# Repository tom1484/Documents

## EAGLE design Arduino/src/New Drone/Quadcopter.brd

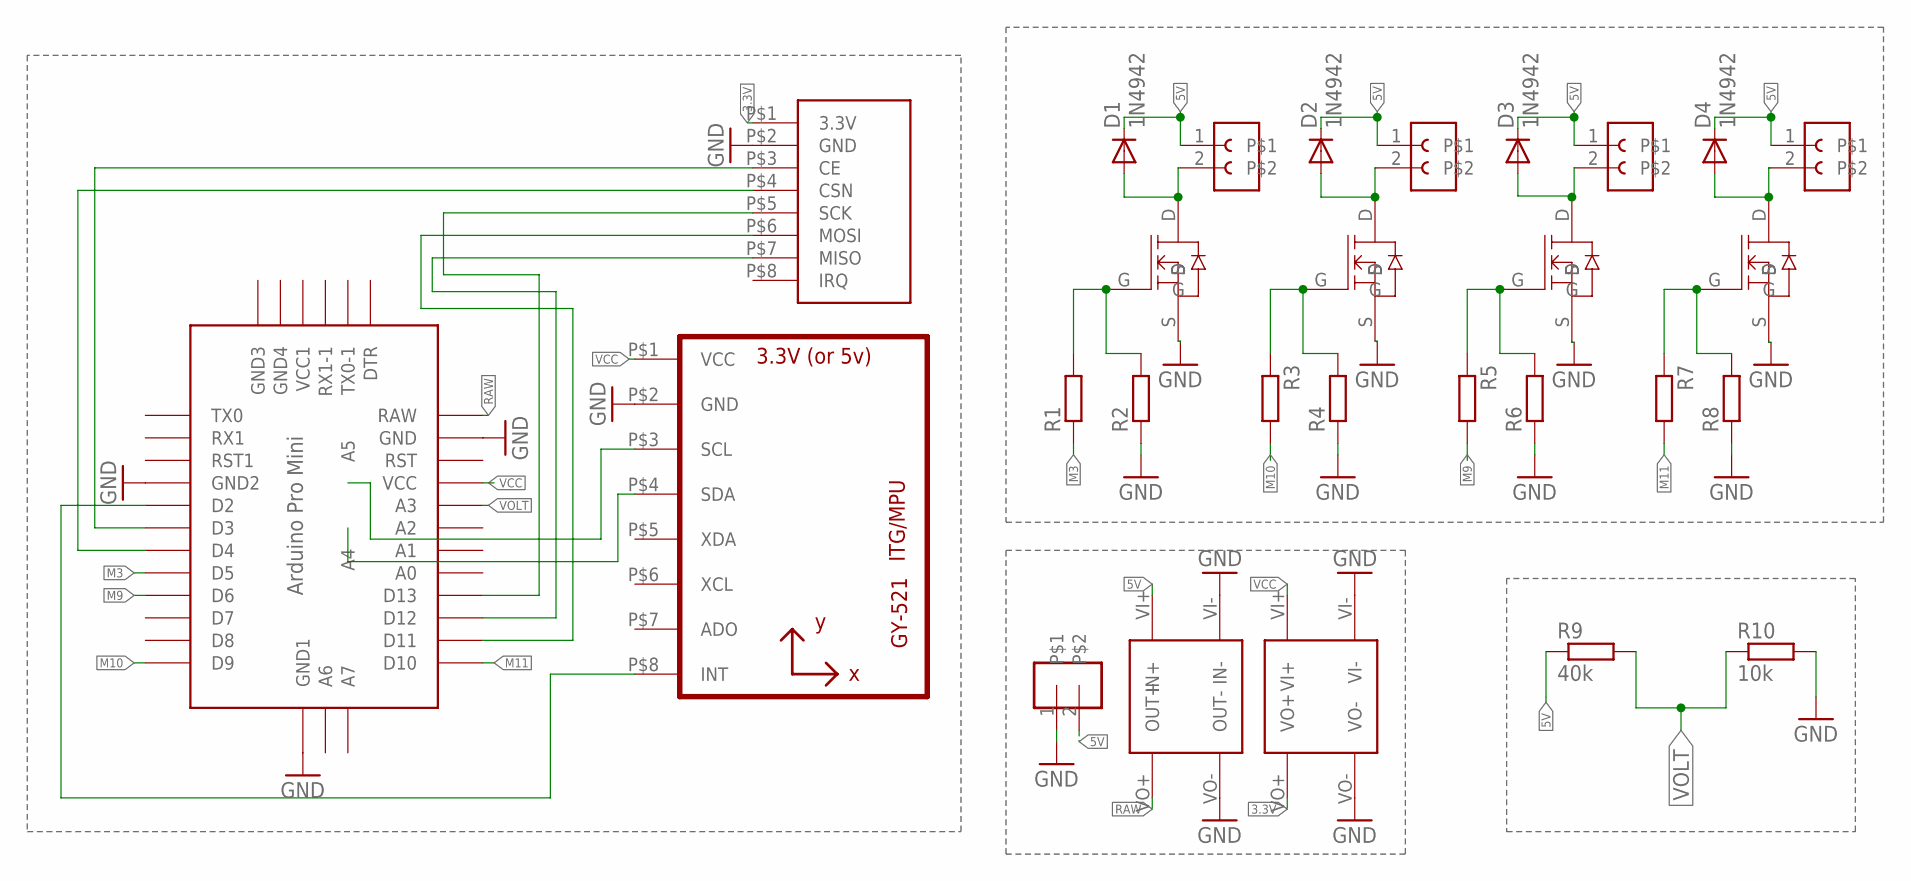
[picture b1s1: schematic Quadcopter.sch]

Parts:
D1, D2, D3, D4: 1N4942; DO41-10
R1, R2, R3, R4, R5, R6, R7, R8: R-EU_R1206; R1206
R9: 40k; R1206
R10: 10k; R1206
U2: GY-521MPU6050; GY-521
U$1, U$2, U$3, U$9: FE02
U$4: ABK-PRO-MINI
U$5, U$7, U$8, U$10: SI2306
U$6: 02; FE05-1
U$11: NRF24L01
U$12: 3.3V
U$13: 5V

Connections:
3.3V: U$11.P$1 (3.3V), U$12.VO+
5V: D1.C, D2.C, D3.C, D4.C, R9.1, U$1.1, U$2.1, U$3.1, U$6.2, U$9.1, U$13.VI+ (IN+)
GND: R2.1, R4.1, R6.1, R8.1, R10.2, U2.P$2 (GND), U$4.P$10 (GND2), U$4.P$20 (GND), U$4.P$33 (GND1), U$5.S, U$6.1, U$7.S, U$8.S, U$10.S, U$11.P$2 (GND), U$12.VI-, U$12.VO-, U$13.VI- (IN-), U$13.VO- (OUT-)
M3: R1.1, U$4.P$14 (D5)
M9: R5.2, U$4.P$15 (D6)
M10: R3.2, U$4.P$18 (D9)
M11: R7.2, U$4.P$30 (D10)
unnamed: R1.2, R2.2, U$7.G
unnamed: D1.A, U$3.2, U$7.D
unnamed: R3.1, R4.2, U$8.G
unnamed: D2.A, U$1.2, U$8.D
unnamed: R5.1, R6.2, U$10.G
unnamed: D3.A, U$9.2, U$10.D
unnamed: R7.1, R8.2, U$5.G
unnamed: D4.A, U$2.2, U$5.D
unnamed: U$4.P$12 (D3), U$11.P$3 (CE)
unnamed: U$4.P$13 (D4), U$11.P$4 (CSN)
unnamed: U$4.P$27 (D13), U$11.P$5 (SCK)
unnamed: U$4.P$28 (D12), U$11.P$7 (MISO)
unnamed: U$4.P$29 (D11), U$11.P$6 (MOSI)
unnamed: U2.P$8 (INT), U$4.P$11 (D2)
unnamed: U2.P$3 (SCL), U$4.P$34 (A5)
unnamed: U2.P$4 (SDA), U$4.P$35 (A4)
RAW: U$4.P$19 (RAW), U$13.VO+ (OUT+)
VCC: U2.P$1 (VCC), U$4.P$22 (VCC), U$12.VI+
VOLT: R9.2, R10.1, U$4.P$23 (A3)

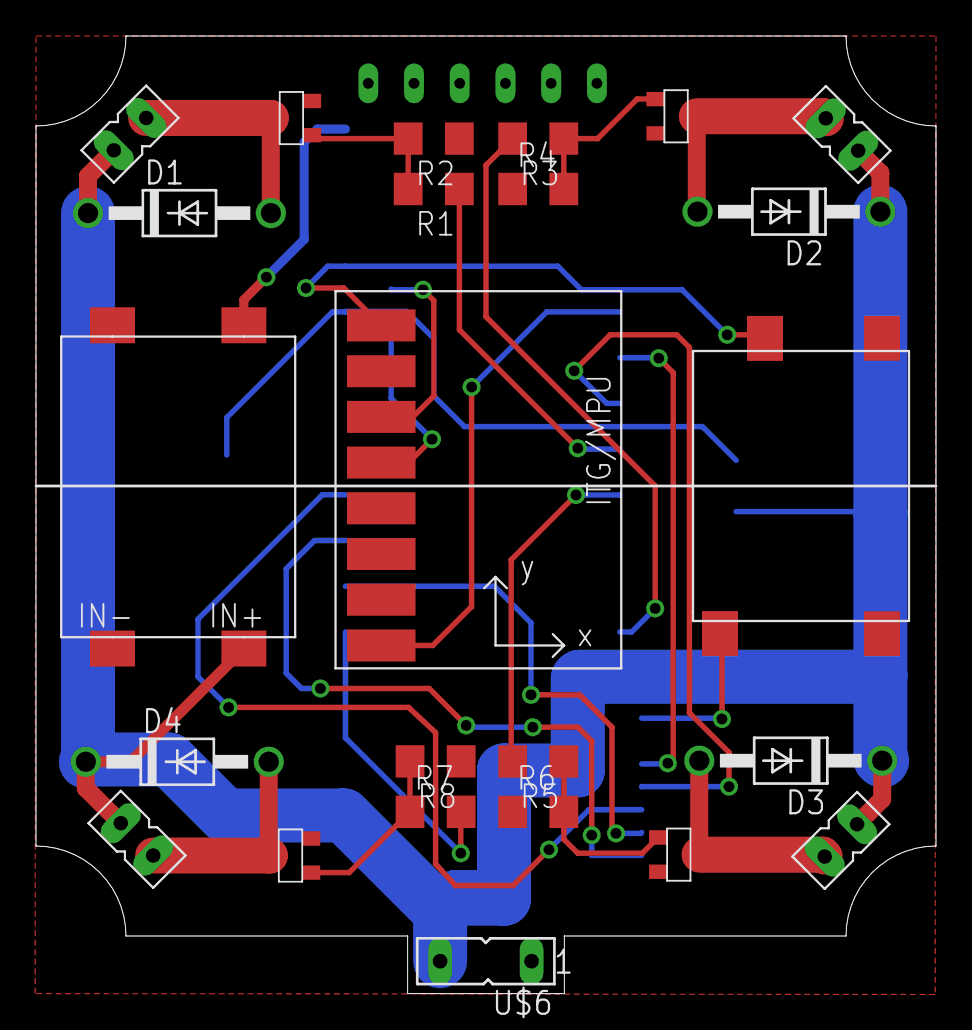
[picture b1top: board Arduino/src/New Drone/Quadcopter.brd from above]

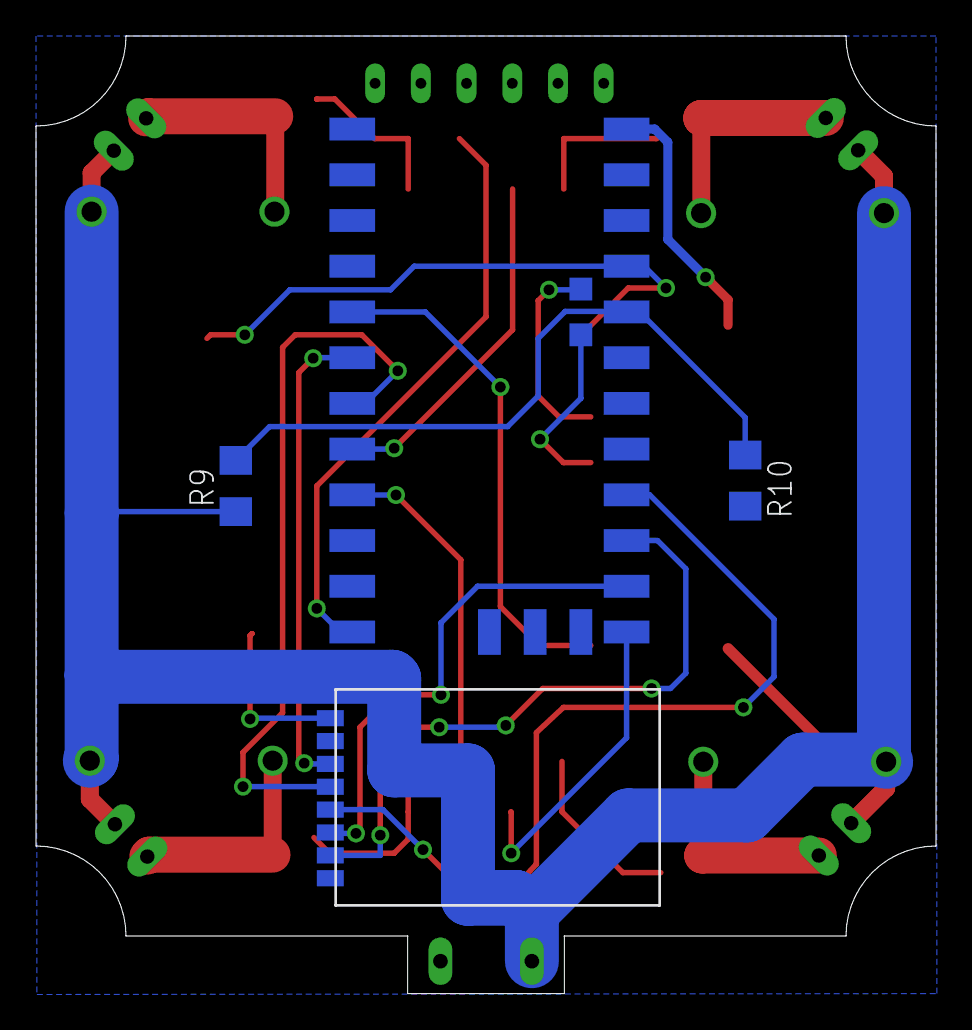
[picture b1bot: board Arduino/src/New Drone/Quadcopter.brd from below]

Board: 2 copper layers, 50.0 x 53.2 mm, 28 parts (4 on the bottom side), 26 nets.

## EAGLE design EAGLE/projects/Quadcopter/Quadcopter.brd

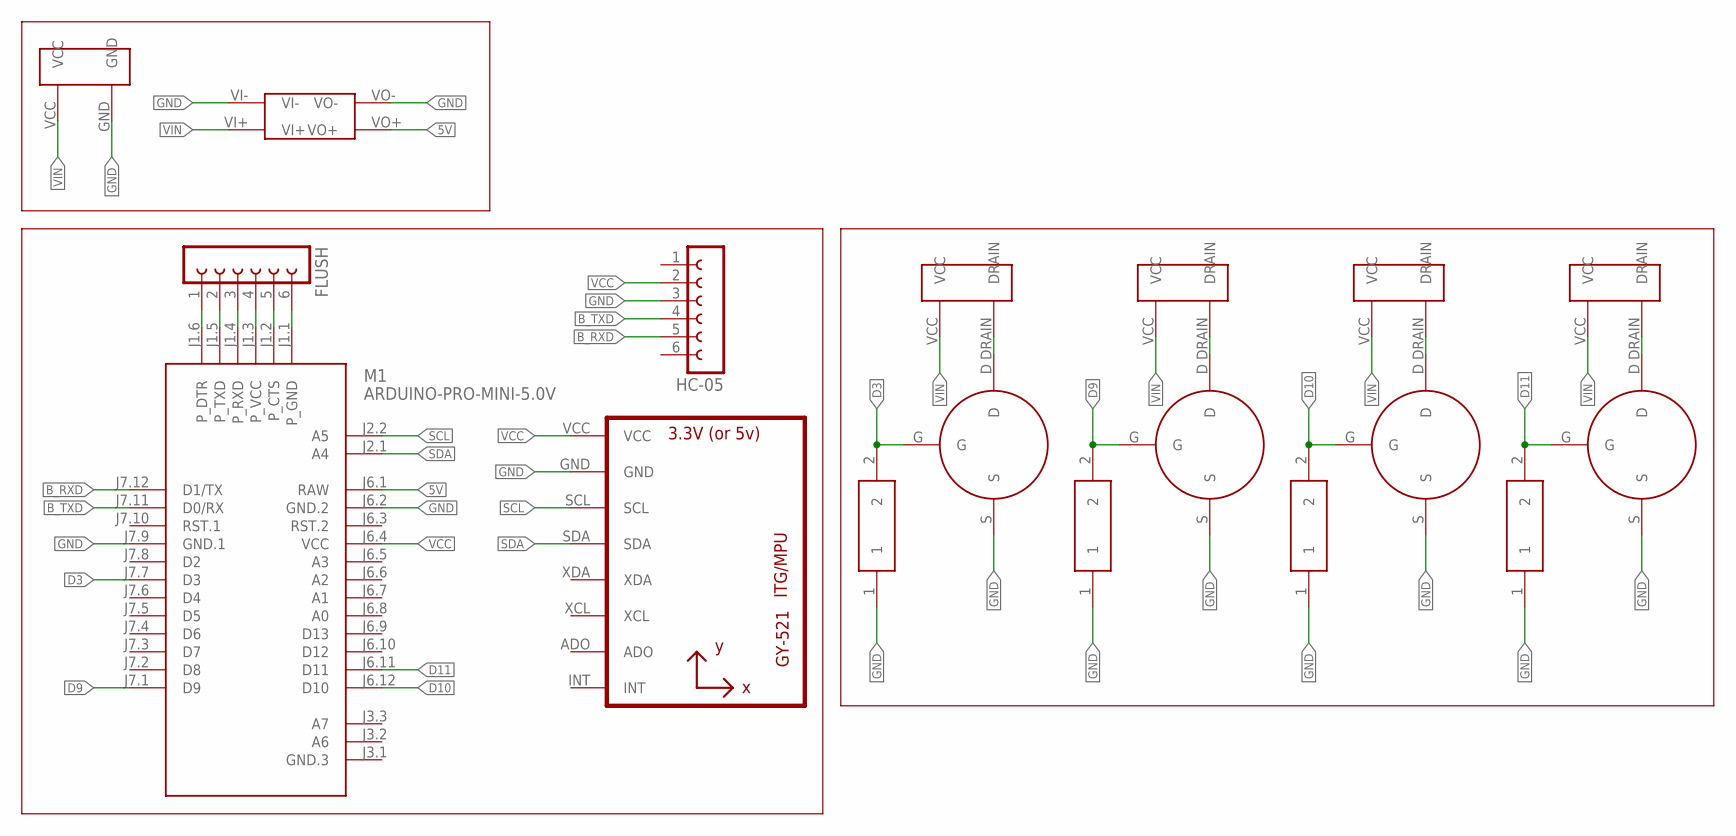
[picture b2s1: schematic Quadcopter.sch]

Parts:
FLUSH: FE06-1; FE06
HC-05: FE06-1; FE06
M1: ARDUINO-PRO-MINI-5.0V; ARDUINO-PRO-MINI
U1: GY-521MPU6050; GY-521
U$1, U$6, U$9, U$12: SI2306
U$2, U$7, U$10, U$13: 1206_RESISTOR
U$3: 5V_TRANSFORMER
U$4: POWER_MAIN
U$5, U$8, U$11, U$14: POWER_MOTOR

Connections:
5V: M1.J6.1 (RAW), U$3.VO+
B_RXD: HC-05.5, M1.J7.12 (D1/TX)
B_TXD: HC-05.4, M1.J7.11 (D0/RX)
D3: M1.J7.7 (D3), U$1.G, U$2.2
D9: M1.J7.1 (D9), U$6.G, U$7.2
D10: M1.J6.12 (D10), U$9.G, U$10.2
D11: M1.J6.11 (D11), U$12.G, U$13.2
GND: HC-05.3, M1.J6.2 (GND.2), M1.J7.9 (GND.1), U1.GND, U$1.S, U$2.1, U$3.VI-, U$3.VO-, U$4.GND, U$6.S, U$7.1, U$9.S, U$10.1, U$12.S, U$13.1
unnamed: FLUSH.1, M1.J1.6 (P_DTR)
unnamed: U$6.D, U$8.DRAIN
unnamed: FLUSH.2, M1.J1.5 (P_TXD)
unnamed: U$9.D, U$11.DRAIN
unnamed: U$1.D, U$5.DRAIN
unnamed: FLUSH.3, M1.J1.4 (P_RXD)
unnamed: U$12.D, U$14.DRAIN
unnamed: FLUSH.4, M1.J1.3 (P_VCC)
unnamed: FLUSH.5, M1.J1.2 (P_CTS)
unnamed: FLUSH.6, M1.J1.1 (P_GND)
SCL: M1.J2.2 (A5), U1.SCL
SDA: M1.J2.1 (A4), U1.SDA
VCC: HC-05.2, M1.J6.4 (VCC), U1.VCC
VIN: U$3.VI+, U$4.VCC, U$5.VCC, U$8.VCC, U$11.VCC, U$14.VCC

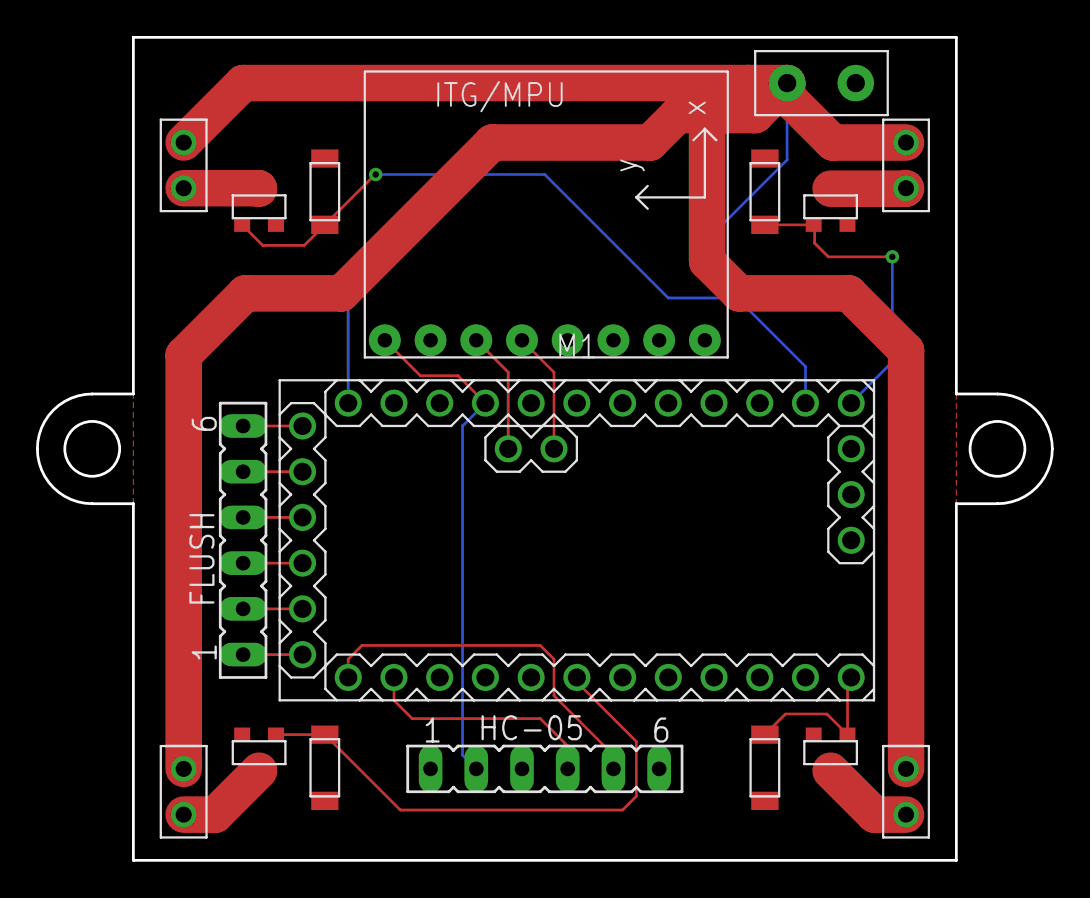
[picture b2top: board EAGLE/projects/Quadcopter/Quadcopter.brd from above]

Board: 2 copper layers, 56.4 x 45.7 mm, 18 parts (1 on the bottom side), 22 nets.

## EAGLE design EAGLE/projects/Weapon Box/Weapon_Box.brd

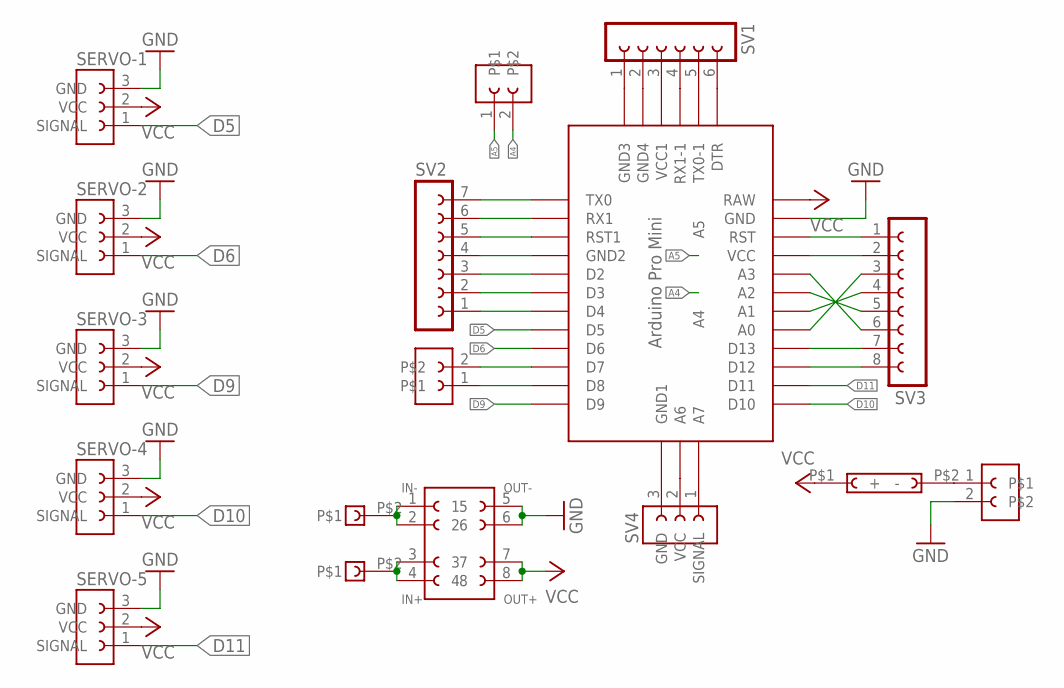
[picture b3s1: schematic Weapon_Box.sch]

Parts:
SERVO-1, SERVO-2, SERVO-3, SERVO-4, SERVO-5: FE05-1
SV1: FE06-1; FE06
SV2: FE07-1; FE07
SV3: FE08-1; FE08
SV4: FE05-1
U$1: ABK-PRO-MINI
U$2: ROWER_SUPPLY
U$3, U$7, U$8: FE02
U$4, U$5: 2018
U$6: 330

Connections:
A4: U$1.A4, U$8.2
A5: U$1.A5, U$8.1
D5: SERVO-1.1 (SIGNAL), U$1.D5
D6: SERVO-2.1 (SIGNAL), U$1.D6
D9: SERVO-3.1 (SIGNAL), U$1.D9
D10: SERVO-4.1 (SIGNAL), U$1.D10
D11: SERVO-5.1 (SIGNAL), U$1.D11
GND: SERVO-1.3 (GND), SERVO-2.3 (GND), SERVO-3.3 (GND), SERVO-4.3 (GND), SERVO-5.3 (GND), U$1.GND, U$2.5, U$2.6, U$7.2
unnamed: SV1.1, U$1.GND2 (GND3)
unnamed: SV1.2, U$1.GND3 (GND4)
unnamed: SV1.3, U$1.VCC1
unnamed: SV1.4, U$1.RX1-1
unnamed: SV1.5, U$1.TX0-1
unnamed: SV1.6, U$1.DTR
unnamed: SV2.1, U$1.D4
unnamed: SV2.2, U$1.D3
unnamed: SV2.3, U$1.D2
unnamed: SV2.4, U$1.GND1 (GND2)
unnamed: SV2.5, U$1.RST1
unnamed: SV2.6, U$1.RX1
unnamed: SV2.7, U$1.TX0
unnamed: SV3.6, U$1.A3
unnamed: SV3.3, U$1.A0
unnamed: SV3.5, U$1.A2
unnamed: SV3.4, U$1.A1
unnamed: SV3.1, U$1.RST
unnamed: SV3.2, U$1.VCC
unnamed: SV3.7, U$1.D13
unnamed: SV3.8, U$1.D12
unnamed: SV4.1 (SIGNAL), U$1.A7
unnamed: SV4.2 (VCC), U$1.A6
unnamed: SV4.3 (GND), U$1.GND4 (GND1)
unnamed: U$1.D8, U$3.1
unnamed: U$1.D7, U$3.2
unnamed: U$2.3, U$2.4, U$5.P$2
unnamed: U$6.P$2 (-), U$7.1
unnamed: U$2.1, U$2.2, U$4.P$2
VCC: SERVO-1.2 (VCC), SERVO-2.2 (VCC), SERVO-3.2 (VCC), SERVO-4.2 (VCC), SERVO-5.2 (VCC), U$1.RAW, U$2.7, U$2.8, U$6.P$1 (+)

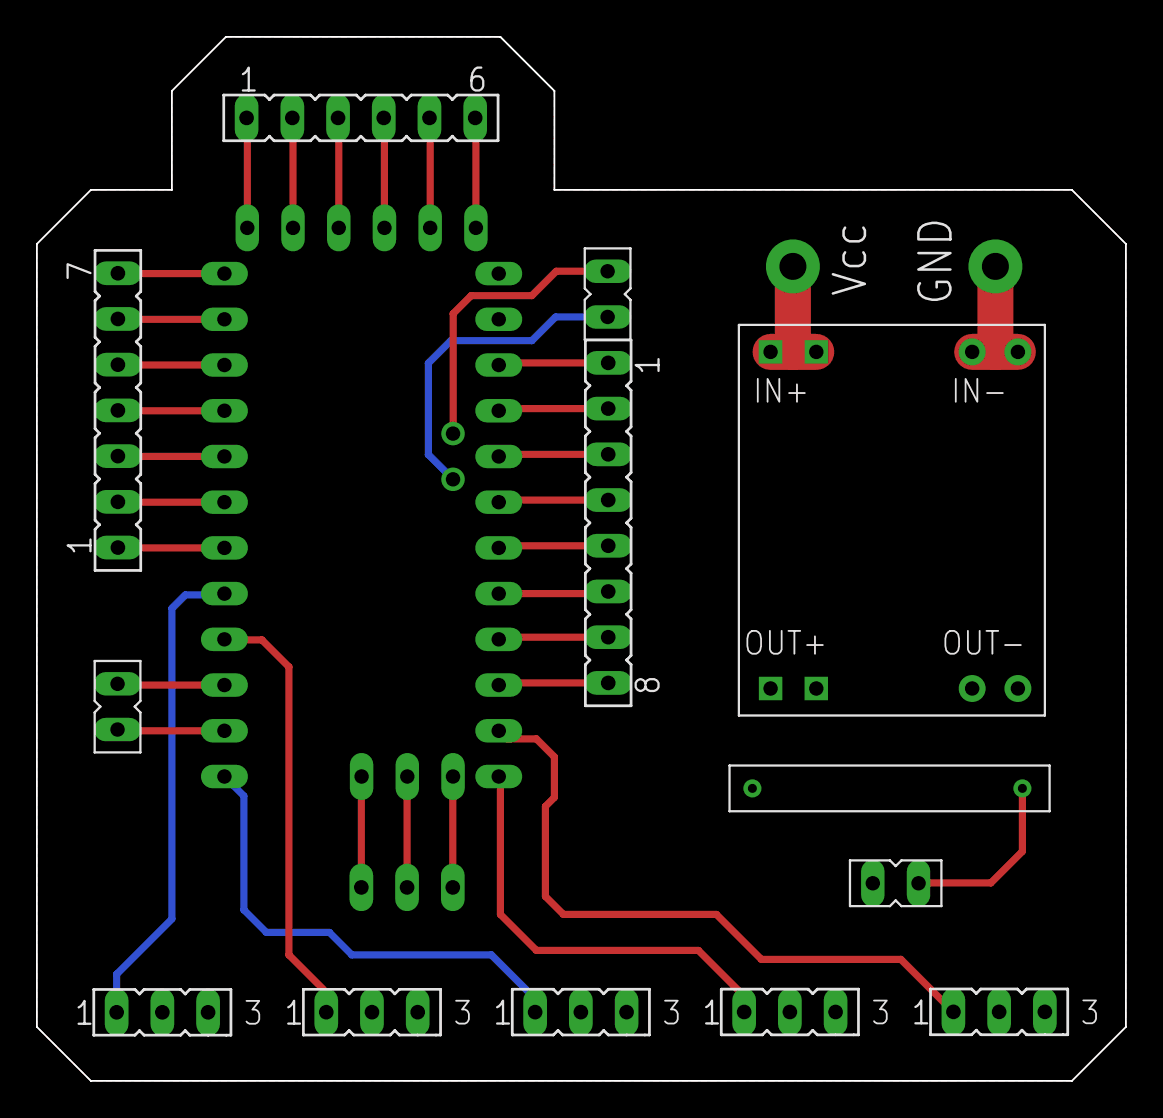
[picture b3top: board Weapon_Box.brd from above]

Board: 2 copper layers, 60.5 x 58.0 mm, 17 parts (1 on the bottom side), 38 nets.

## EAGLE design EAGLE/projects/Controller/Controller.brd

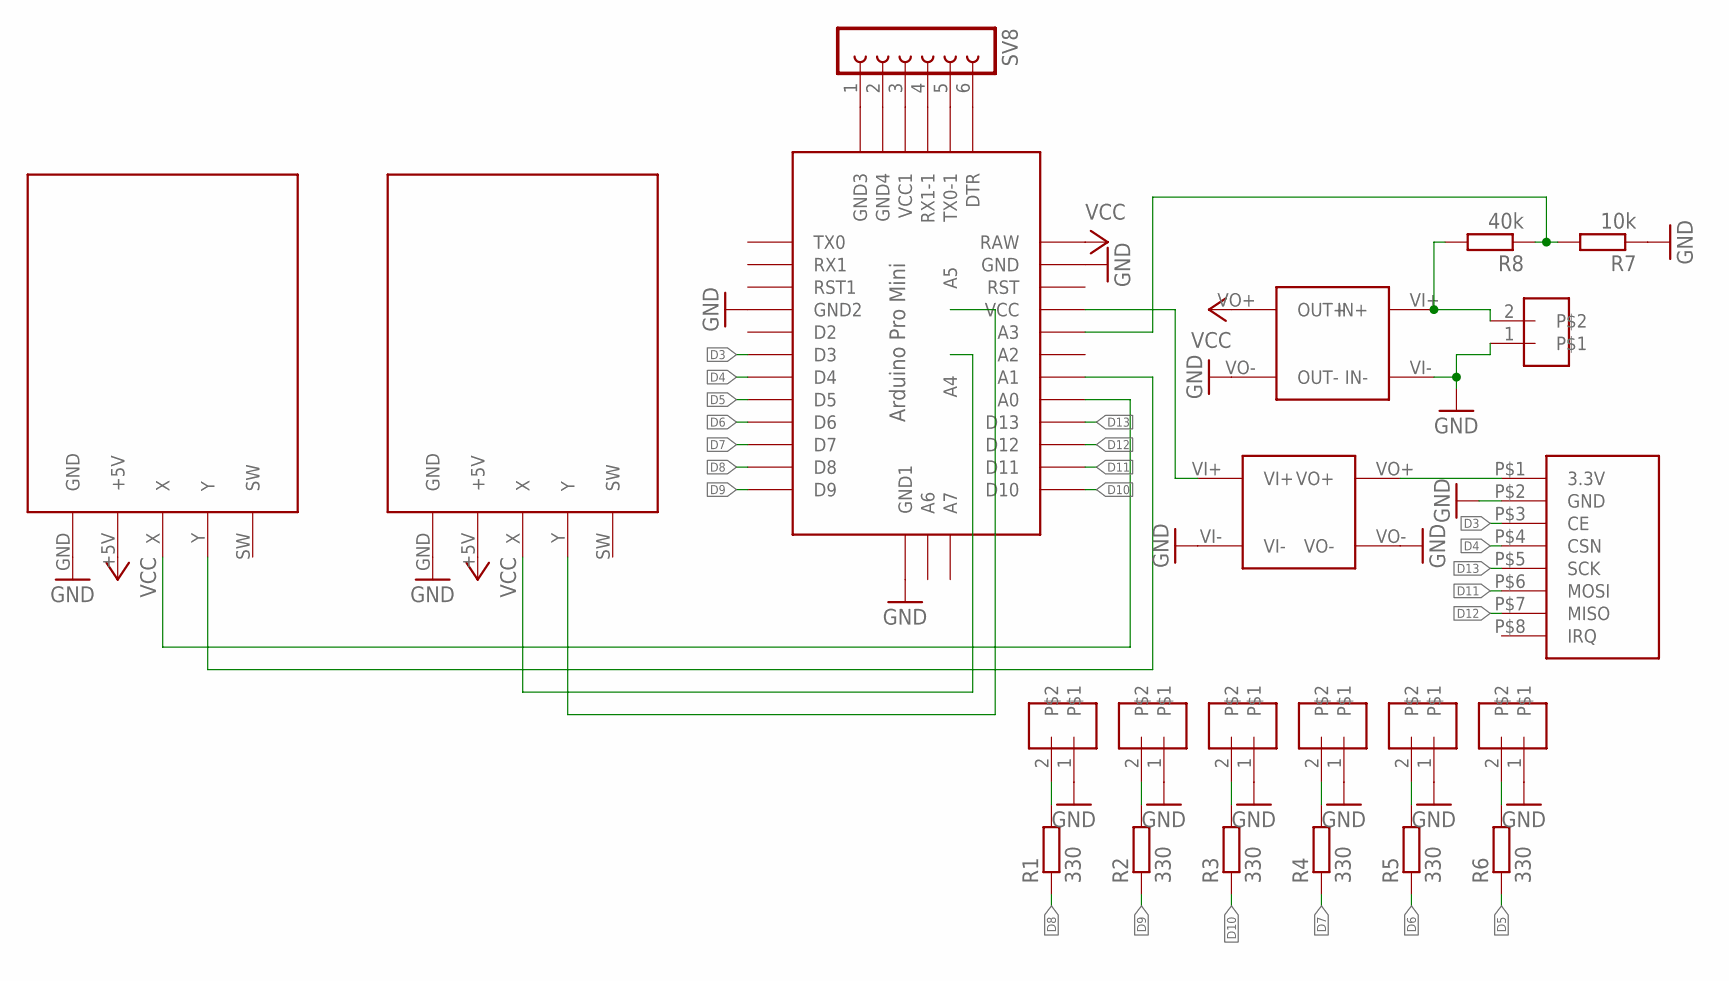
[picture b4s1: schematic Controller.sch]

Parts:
R1, R2, R3, R4, R5, R6: 330; R1206
R7: 10k; R1206
R8: 40k; R1206
SV1, SV2, SV3, SV4, SV5, SV6, SV7: FE05-1
SV8: FE06-1; FE06
U$1, U$2: JOYSTICK
U$4: ABK-PRO-MINI
U$5: NRF24L01
U$7: 3.3V
U$8: 5V

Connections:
D3: U$4.P$12 (D3), U$5.P$3 (CE)
D4: U$4.P$13 (D4), U$5.P$4 (CSN)
D5: R6.1, U$4.P$14 (D5)
D6: R5.1, U$4.P$15 (D6)
D7: R4.1, U$4.P$16 (D7)
D8: R1.1, U$4.P$17 (D8)
D9: R2.1, U$4.P$18 (D9)
D10: R3.1, U$4.P$30 (D10)
D11: U$4.P$29 (D11), U$5.P$6 (MOSI)
D12: U$4.P$28 (D12), U$5.P$7 (MISO)
D13: U$4.P$27 (D13), U$5.P$5 (SCK)
GND: R7.1, SV1.1, SV2.1, SV3.1, SV4.1, SV5.1, SV6.1, SV7.1, U$1.GND, U$2.GND, U$4.P$10 (GND2), U$4.P$20 (GND), U$4.P$33 (GND1), U$5.P$2 (GND), U$7.VI-, U$7.VO-, U$8.VI- (IN-), U$8.VO- (OUT-)
unnamed: U$1.X, U$4.P$26 (A0)
unnamed: U$1.Y, U$4.P$25 (A1)
unnamed: U$2.X, U$4.P$35 (A4)
unnamed: U$2.Y, U$4.P$34 (A5)
unnamed: R8.2, SV1.2, U$8.VI+ (IN+)
unnamed: U$4.P$22 (VCC), U$7.VI+
unnamed: U$5.P$1 (3.3V), U$7.VO+
unnamed: R1.2, SV7.2
unnamed: R2.2, SV6.2
unnamed: R3.2, SV5.2
unnamed: R4.2, SV4.2
unnamed: R5.2, SV3.2
unnamed: R6.2, SV2.2
unnamed: R7.2, R8.1, U$4.P$23 (A3)
unnamed: SV8.1, U$4.P$1 (GND3)
unnamed: SV8.2, U$4.P$2 (GND4)
unnamed: SV8.3, U$4.P$3 (VCC1)
unnamed: SV8.4, U$4.P$4 (RX1-1)
unnamed: SV8.5, U$4.P$5 (TX0-1)
unnamed: SV8.6, U$4.P$6 (DTR)
VCC: U$1.+5V, U$2.+5V, U$4.P$19 (RAW), U$8.VO+ (OUT+)

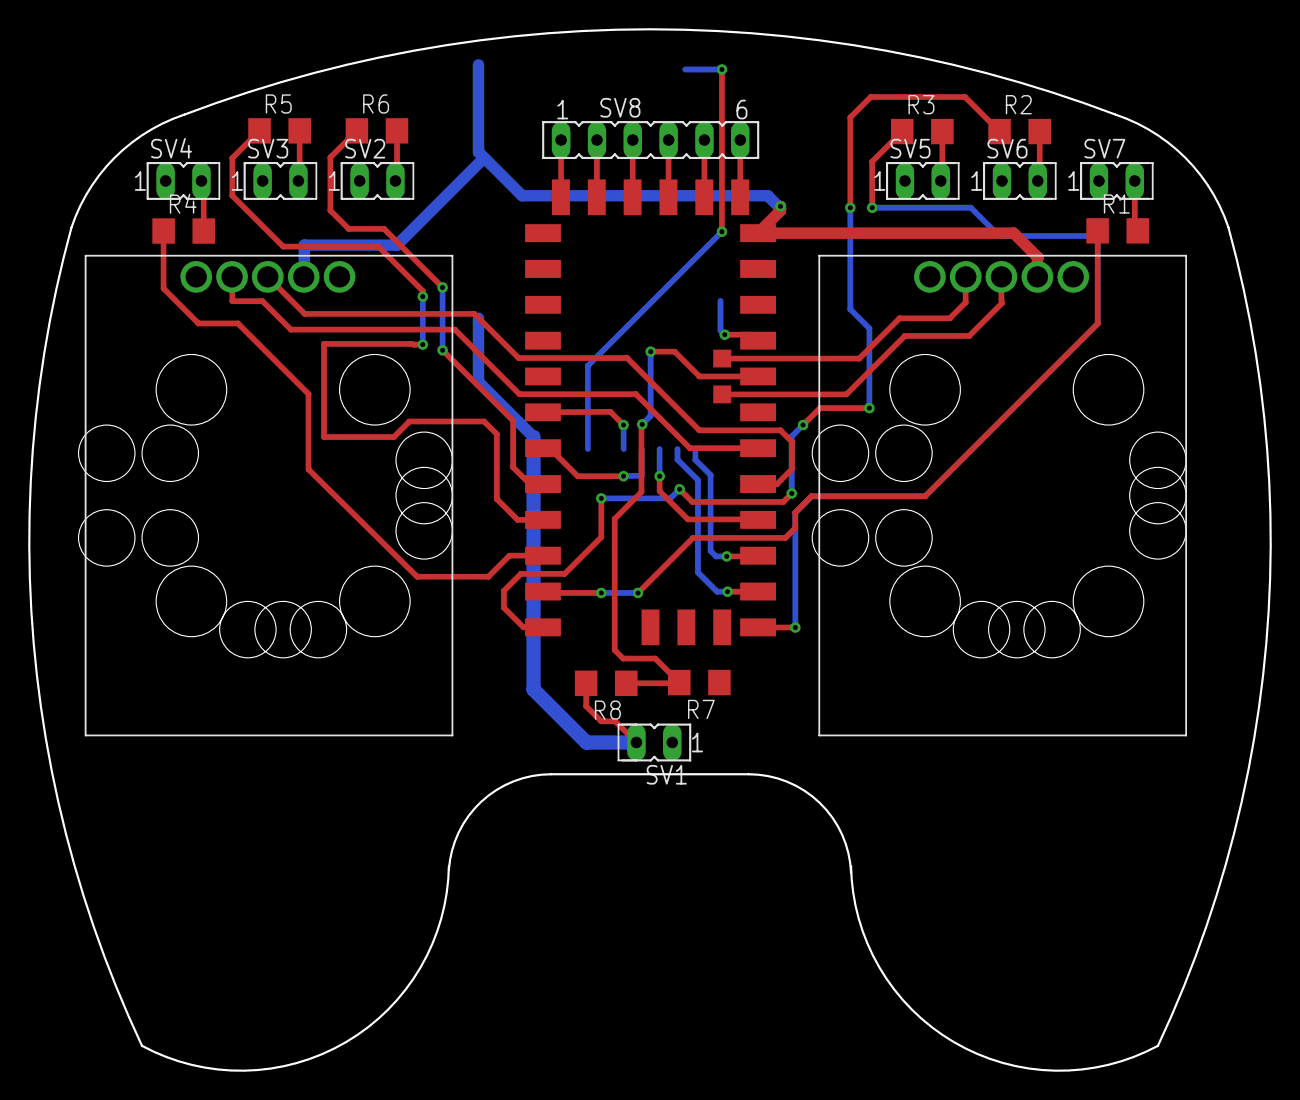
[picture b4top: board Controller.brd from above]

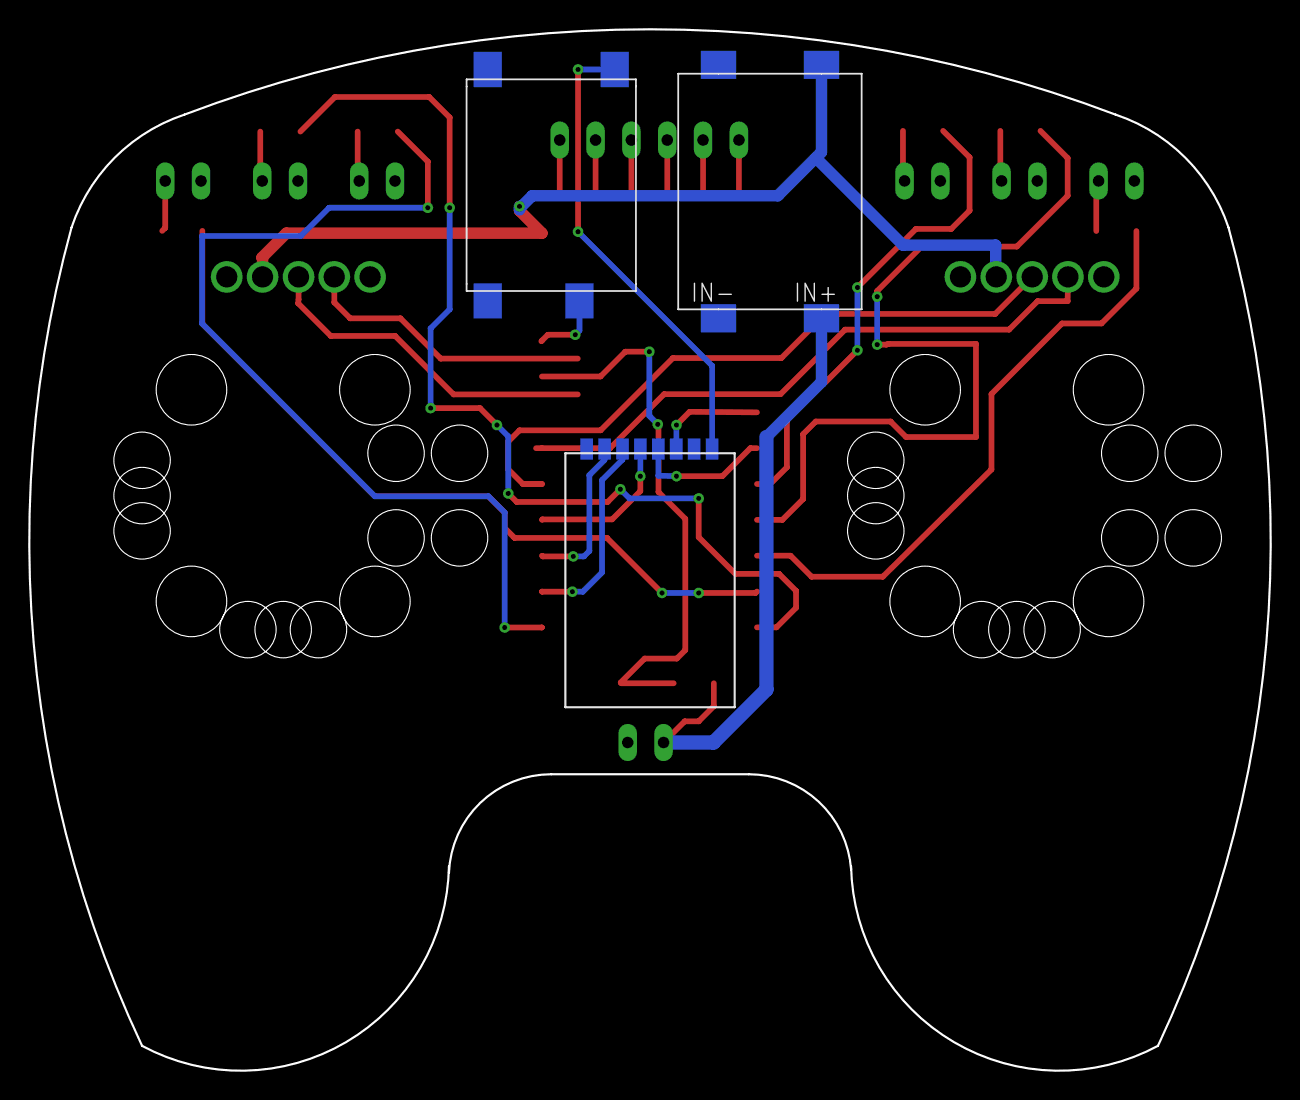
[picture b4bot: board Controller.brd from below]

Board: 2 copper layers, 88.0 x 73.8 mm, 22 parts (3 on the bottom side), 33 nets.

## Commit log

2021-11-23 Clear history
2021-12-04 'Update'

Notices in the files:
parts and their libraries:
diy-modules: Released under the Creative Commons Attribution 4.0 International License: http://creativecommons.org/licenses/by/4.0
